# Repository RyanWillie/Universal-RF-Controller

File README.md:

# Universal-RF-Controller
As a continuation of my studies i aimed to work on a project that could utlise both aspects of my computer science and electrical engineering knowledge, as well as my interest in 3D printing. I decided upon designing an autonomous hexapod robot, which would allow for all aspects to be utilised. In order to be able to control the hexapod remotely i would require a RF controller to communicate with it wirelessly, this also presented an opportunity to tackle a much easier project first before attempting the more complex task.

  - **Computer Science** - Programming the RF Controller and creating/training the machine learning algorithms that will drive the hexapod.
  - **Electrical Engineering ** - Determining the electrical requirements, designing the circuit and PCBs, Soldering the components
  - **3D Printing** - The enclosures for both the RF Controller and the Hexapod robot are designed within Fusion360 and 3D printed using a few different materials
  
The process for designing and manufacturing the RF controller required a few revisions until it fully satisfied the design requirements they are:
  - Two joysticks for control
  - Display and rotary encoder for menu/mode selection
  - Gyroscope/accelerometer for alternative controls
  - Power switch
  - Microcontroller
  - RF Transciever
  
  ## Component Selection
  The main principle of the component selection was to use readily available components with libraries available for easy and quick setup,as well as preferring breakout boards so that the components can be easily salvaged/replaced for other projects when it is not needed. Therefore the microcontroller will be an Arduino nano, and the popular NRF24L01 transciever as the available libary makes connection extremely easy.

  **BOM**
  - Arduino Nano
  - OLED Screen
  - MPU6050 Breakout
  - Rotary Encoder
  - 2x COM09032 (Joystick)
  - 2x 200nF Capacitor
  - 10uF Capacitor
  - NRF24L01 Transciever
  - Toggle Switch

   ## Proof of concept
   Before desiging the PCB i confirmed that the designed circuit was connected correctly and worked as intended, the circuit was constructed on breadboard, this can be seen in the below image:

   ## PCB Design and Manufacturing
   The open source program [KiCad](https://kicad.org/) was used as the design software for the PCB, it is a 2 layer board designed to meet JLCPCB's requirements.  As the board is a one off the space and shape requirements are purely to achieve the smallest practical footprint.

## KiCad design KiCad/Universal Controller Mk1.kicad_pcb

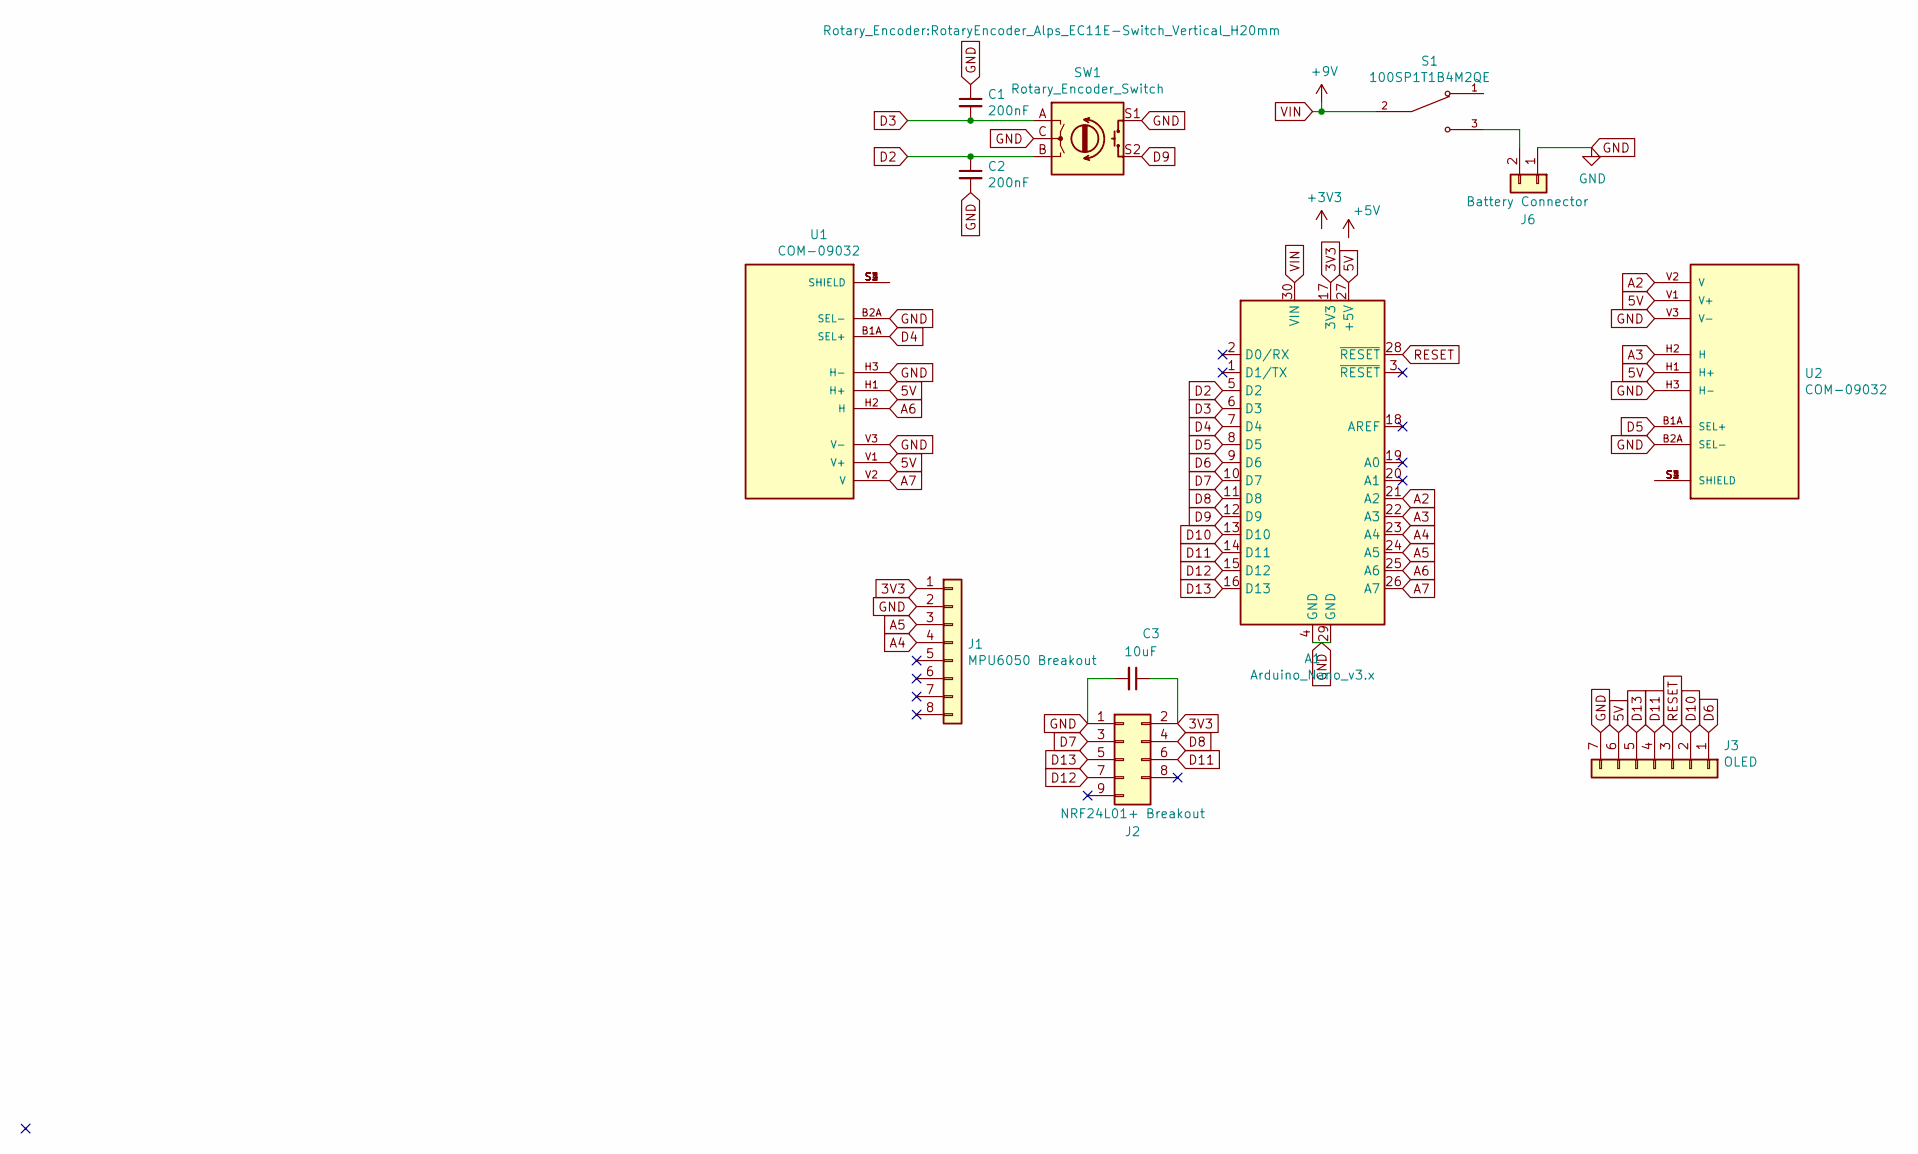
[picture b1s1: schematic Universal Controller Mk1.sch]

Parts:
A1: Arduino_Nano_v3.x; Arduino_Nano
C1, C2: 200nF; CP_Radial_Tantal_D8.0mm_P5.00mm
C3: 10uF; CP_Radial_Tantal_D8.0mm_P5.00mm
J1: MPU6050 Breakout; PinHeader_1x08_P2.54mm_Vertical
J2: NRF24L01+ Breakout; PinHeader_2x05_P2.54mm_Vertical
J3: OLED; PinHeader_1x07_P2.54mm_Vertical
J6: Battery Connector; PinHeader_1x02_P2.54mm_Vertical
S1: 100SP1T1B4M2QE; SW_100SP1T1B4M2QE; PARTREV E
SW1: Rotary_Encoder_Switch; RotaryEncoder_Alps_EC11E-Switch_Vertical_H20mm
U1, U2: COM-09032; XDCR_COM-09032; PARTREV N/A

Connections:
3V3: A1.17 (3V3), C3.1, J1.1, J2.2
5V: A1.27 (+5V), J3.6, U1.H1 (H+), U1.V1 (V+), U2.H1 (H+), U2.V1 (V+)
A2: A1.21 (A2), U2.V2 (V)
A3: A1.22 (A3), U2.H2 (H)
A4: A1.23 (A4), J1.4
A5: A1.24 (A5), J1.3
A6: A1.25 (A6), U1.H2 (H)
A7: A1.26 (A7), U1.V2 (V)
D2: A1.5 (D2), C2.1, SW1.B
D3: A1.6 (D3), C1.2, SW1.A
D4: A1.7 (D4), U1.B1A (SEL+)
D5: A1.8 (D5), U2.B1A (SEL+)
D6: A1.9 (D6), J3.1
D7: A1.10 (D7), J2.3
D8: A1.11 (D8), J2.4
D9: A1.12 (D9), SW1.S2
D10: A1.13 (D10), J3.2
D11: A1.14 (D11), J2.6, J3.4
D12: A1.15 (D12), J2.7
D13: A1.16 (D13), J2.5, J3.5
GND: A1.4 (GND), A1.29 (GND), C1.1, C2.2, C3.2, J1.2, J2.1, J3.7, J6.1, SW1.C, SW1.S1, U1.B2A (SEL-), U1.H3 (H-), U1.V3 (V-), U2.B2A (SEL-), U2.H3 (H-), U2.V3 (V-)
unnamed: J6.2, S1.3
unnamed: U1.S1 (SHIELD), U1.S2 (SHIELD), U1.S3 (SHIELD), U1.S4 (SHIELD)
unnamed: U2.S1 (SHIELD), U2.S2 (SHIELD), U2.S3 (SHIELD), U2.S4 (SHIELD)
RESET: A1.28 (~RESET), J3.3
VIN: A1.30 (VIN), S1.2

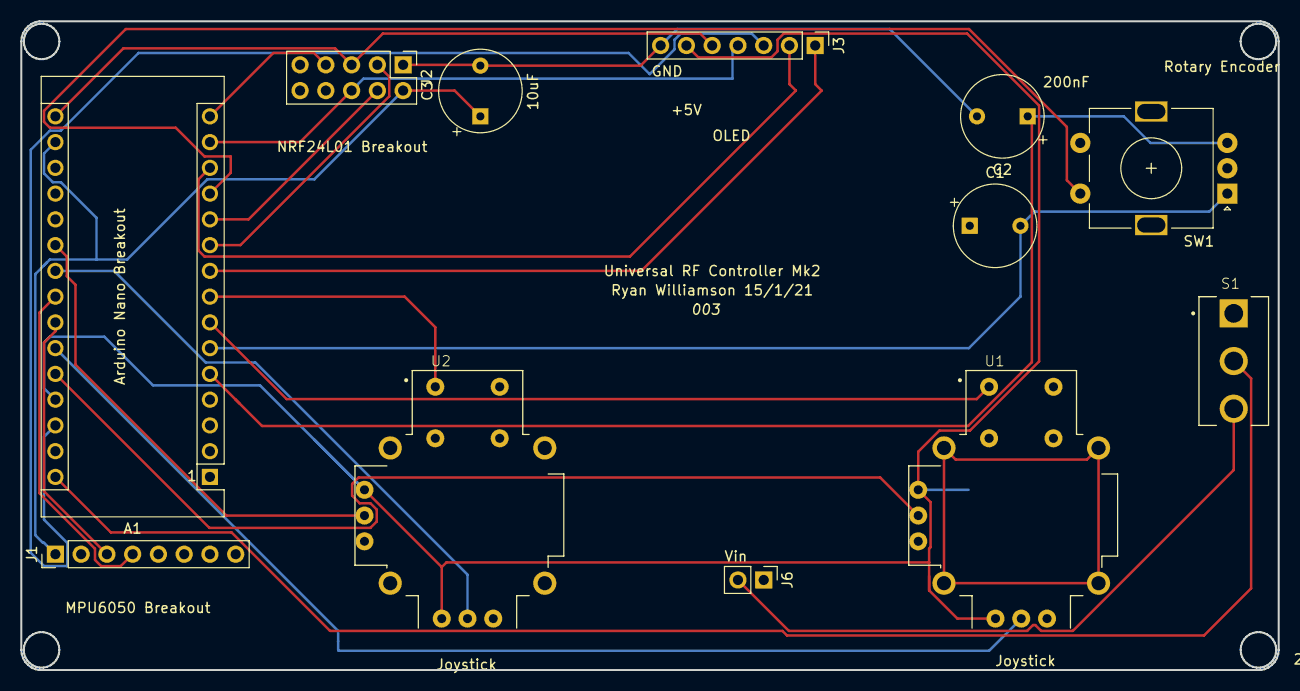
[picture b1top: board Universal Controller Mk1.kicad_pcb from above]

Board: 2 copper layers, 124.0 x 64.0 mm, 12 parts (0 on the bottom side), 26 nets.

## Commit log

2021-02-06 Updated Readme with project information
2021-02-06 Controller Mk2 design files and images
2021-02-06 Adding in schematic Image
2021-02-06 Updating Readme with images
